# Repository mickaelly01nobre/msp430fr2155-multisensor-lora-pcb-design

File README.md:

# Nó Multissensor LoRa com MSP430 (PCB IoT de Baixo Consumo)

## 📌 Visão Geral
Este projeto apresenta o desenvolvimento de um **nó IoT multissensor de baixo consumo** baseado no **microcontrolador MSP430FR2155**, integrando múltiplos sensores ambientais e de monitoramento em uma PCB personalizada.

O sistema foi projetado com foco em **eficiência energética**, **comunicação sem fio** e **sensoriamento modular**, sendo adequado para aplicações como monitoramento ambiental, agricultura inteligente e sensoriamento remoto.

---

## ⚙️ Funcionalidades
- 🔋 **Projeto de Baixo Consumo**
  - Modos de sleep para sensores e MCU
  - Gerenciamento de energia otimizado para operação com bateria

- 📡 **Comunicação LoRa**
  - Transmissão de dados sem fio de longo alcance e baixo consumo

- 🌡️ **Integração Multissensor**
  - Sensor de temperatura e umidade
  - Sensor de gás
  - Sensor de peso (interface com célula de carga)

- 🔌 **Alimentação Flexível**
  - Entrada USB
  - Operação via bateria

- 🔄 **Confiabilidade do Sistema**
  - Circuito de reset externo para estabilidade do MCU
  - Interface de programação/debug

---

## 🧠 Arquitetura de Hardware
- **Microcontrolador:** MSP430FR2155  
- **Comunicação:** Módulo LoRa  
- **Sensores:**
  - Temperatura & Umidade  
  - Sensor de Gás  
  - Sensor de Peso (Célula de Carga)  

- **Sistema de Alimentação:**
  - Entrada USB  
  - Entrada por bateria  
  - Circuito de comutação de energia  

- **Outros Circuitos:**
  - Controle de alimentação dos sensores (sleep/power gating)  
  - Circuito de reset  
  - Interface de programação  

---

## 🔋 Estratégia de Baixo Consumo
O sistema foi projetado com foco em **eficiência energética**, incluindo:
- Ativação seletiva dos sensores (controle de modo sleep)
- Uso dos modos de baixo consumo do MSP430 (LPM)
- Seleção eficiente da fonte de energia (USB/Bateria)
- Redução do consumo em estado ocioso

---

## 🖥️ Projeto da PCB
- PCB personalizada desenvolvida para integração compacta  
- Separação das seções analógica e digital  
- Técnicas de redução de ruído para maior precisão dos sensores  
- Projetado utilizando (adicione seu software aqui: KiCad / Altium / etc.)  

---

## 📊 Aplicações
- Monitoramento ambiental  
- Agricultura inteligente  
- Sensoriamento industrial  
- Nós IoT remotos  

---

## 🚀 Melhorias Futuras
- Integração com plataformas em nuvem  
- Dashboard web/mobile  
- Suporte a energy harvesting  
- Otimização de firmware para ultra baixo consumo  

---

## 🛠️ Tecnologias & Habilidades
- Sistemas Embarcados  
- Projeto de PCB  
- Eletrônica de Baixo Consumo  
- Integração de Sensores  
- Sistemas IoT  
- Comunicação LoRa  

---

## 📷 Preview

---

## 👩‍💻 Autor
Desenvolvido por Mickaelly Freitas Nobre

---

# MSP430 LoRa Multisensor Node (Low Power IoT PCB)

## 📌 Overview
This project presents the design and development of a **low-power multisensor IoT node** based on the **MSP430FR2155 microcontroller**, integrating multiple environmental and monitoring sensors into a custom PCB.

The system is designed for **energy efficiency**, **wireless communication**, and **modular sensing**, making it suitable for applications such as environmental monitoring, smart agriculture, and remote sensing.

---

## ⚙️ Features
- 🔋 **Low Power Design**
  - Sleep modes for sensors and MCU
  - Power management optimized for battery operation

- 📡 **LoRa Communication**
  - Long-range, low-power wireless data transmission

- 🌡️ **Multisensor Integration**
  - Temperature and humidity sensor
  - Gas sensor
  - Weight sensor (load cell interface)

- 🔌 **Flexible Power Supply**
  - USB power input
  - Battery-powered operation

- 🔄 **System Reliability**
  - External reset circuit for MCU stability
  - Programming/debug interface

---

## 🧠 Hardware Architecture
- **Microcontroller:** MSP430FR2155  
- **Communication:** LoRa module  
- **Sensors:**
  - Temperature & Humidity  
  - Gas Sensor  
  - Weight Sensor (Load Cell)  

- **Power System:**
  - USB input  
  - Battery input  
  - Power switching circuit  

- **Other Circuits:**
  - Sensor power gating (sleep control)  
  - Reset circuit  
  - Programming interface  

---

## 🔋 Low Power Strategy
The system was designed with a focus on **energy efficiency**, including:
- Selective sensor activation (sleep mode control)
- MSP430 low-power modes (LPM)
- Efficient power path selection (USB/Battery)
- Reduced idle consumption

---

## 🖥️ PCB Design
- Custom PCB developed for compact integration  
- Separation of analog and digital sections  
- Noise reduction techniques for sensor accuracy  
- Designed using (add your software here: KiCad / Altium / etc.)

---

## 📊 Applications
- Environmental monitoring  
- Smart agriculture  
- Industrial sensing  
- Remote IoT nodes  

---

## 🚀 Future Improvements
- Integration with cloud platforms  
- Mobile/web dashboard  
- Energy harvesting support  
- Firmware optimization for ultra-low power  

---

---

## 🛠️ Technologies & Skills
- Embedded Systems  
- PCB Design  
- Low Power Electronics  
- Sensor Integration  
- IoT Systems  
- LoRa Communication  

---

## 📷 Preview

---

## 👩‍💻 Author
Developed by Mickaelly Freitas Nobre

---

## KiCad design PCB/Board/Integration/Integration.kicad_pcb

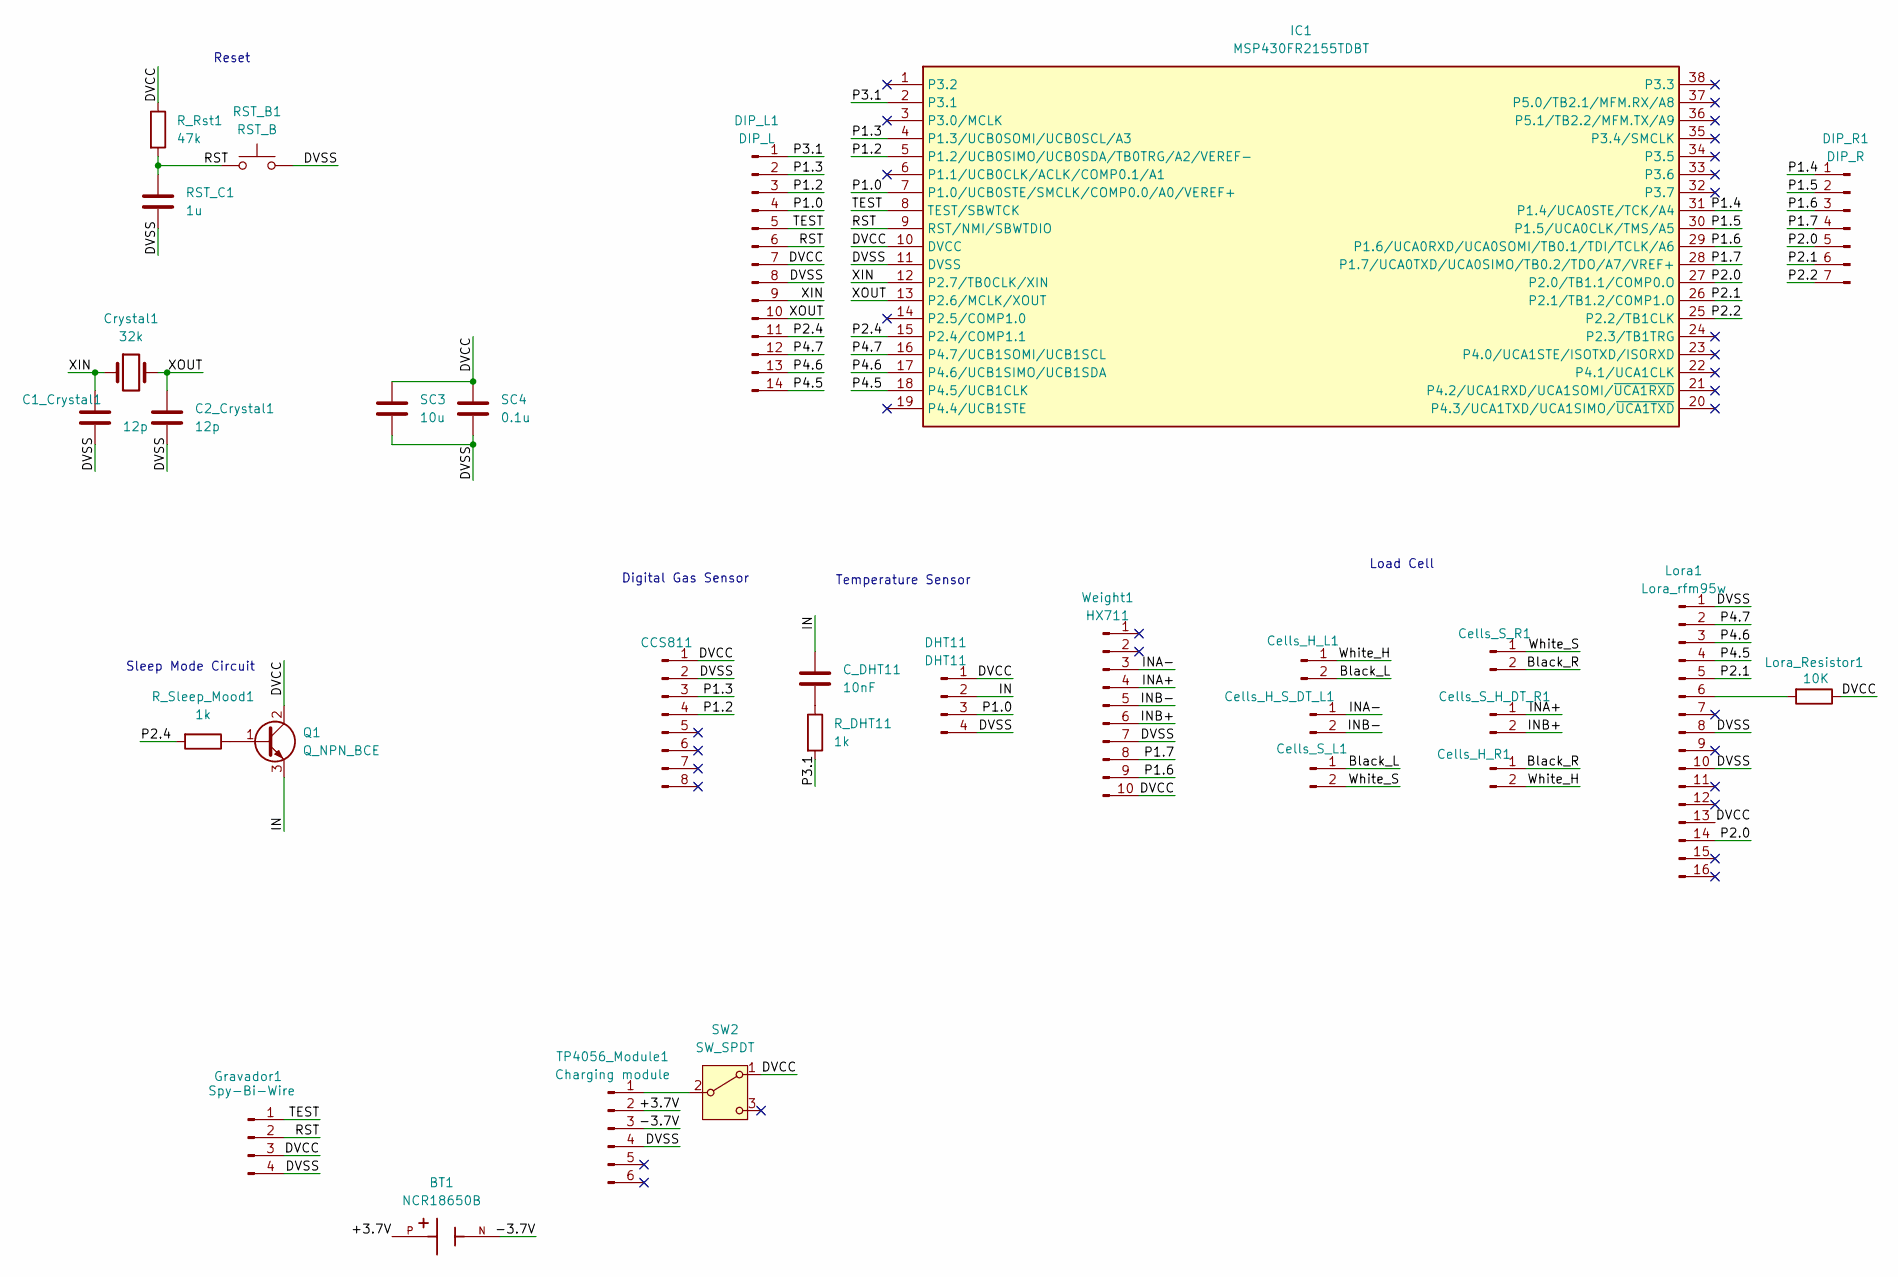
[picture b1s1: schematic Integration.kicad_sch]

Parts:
BT1: NCR18650B; BAT_1042; PARTREV E
C1_Crystal1, C2_Crystal1: 12p; C_Disc_D5.0mm_W2.5mm_P5.00mm
CCS811: Conn_01x08_Pin; MODULO_GAS
C_DHT11: 10nF; C_Disc_D3.0mm_W1.6mm_P2.50mm
Cells_H_L1: Conn_01x02_Pin; JST_XH_B2B-XH-A_1x02_P2.50mm_Vertical
Cells_H_R1: Conn_01x02_Pin; JST_XH_B2B-XH-A_1x02_P2.50mm_Vertical
Cells_H_S_DT_L1: Conn_01x02_Pin; JST_XH_B2B-XH-A_1x02_P2.50mm_Vertical
Cells_S_H_DT_R1: Conn_01x02_Pin; JST_XH_B2B-XH-A_1x02_P2.50mm_Vertical
Cells_S_L1: Conn_01x02_Pin; JST_XH_B2B-XH-A_1x02_P2.50mm_Vertical
Cells_S_R1: Conn_01x02_Pin; JST_XH_B2B-XH-A_1x02_P2.50mm_Vertical
Crystal1: 32k; R_Axial_DIN0204_L3.6mm_D1.6mm_P1.90mm_Vertical
DHT11: DHT11; Aosong_DHT11_5.5x12.0_P2.54mm
DIP_L1: DIP_L; PinSocket_1x14_P2.54mm_Vertical
DIP_R1: DIP_R; PinSocket_1x07_P2.54mm_Vertical
Gravador1: Spy-Bi-Wire; JST_XH_B4B-XH-A_1x04_P2.50mm_Vertical
IC1: MSP430FR2155TDBT; SOP50P640X120-38N; Mouser Part Number 595-MSP430FR2155TDBT
Lora1: Lora_rfm95w; HOPERF_RFM9XW_THT
Lora_Resistor1: 10K; R_Axial_DIN0204_L3.6mm_D1.6mm_P1.90mm_Vertical
Q1: Q_NPN_BCE; PinSocket_1x03_P2.54mm_Vertical
RST_B1: RST_B; SW_PUSH_6mm
RST_C1: 1u; CP_Radial_D8.0mm_P5.00mm
R_DHT11: 1k; R_Axial_DIN0204_L3.6mm_D1.6mm_P1.90mm_Vertical
R_Rst1: 47k; R_Axial_DIN0204_L3.6mm_D1.6mm_P1.90mm_Vertical
R_Sleep_Mood1: 1k; R_Axial_DIN0204_L3.6mm_D1.6mm_P1.90mm_Vertical
SC3: 10u; CP_Radial_D8.0mm_P3.50mm
SC4: 0.1u; C_Disc_D5.0mm_W2.5mm_P5.00mm
SW2: SW_SPDT; SW_PUSH_1P1T_6x3.5mm_H5.0_APEM_MJTP1250
TP4056_Module1: Charging module; TP4056
Weight1: HX711; MODULO_HX711

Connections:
/+3.7V: BT1.P, TP4056_Module1.2
/-3.7V: BT1.N, TP4056_Module1.3
/Black_L: Cells_H_L1.2, Cells_S_L1.1
/Black_R: Cells_H_R1.1, Cells_S_R1.2
/DVCC: CCS811.1, DHT11.1, DIP_L1.7, Gravador1.3, IC1.10 (DVCC), Lora1.13, Lora_Resistor1.1, Q1.2 (C), R_Rst1.1, SC3.1, SC4.1, SW2.1 (A), Weight1.10
/DVSS: C1_Crystal1.2, C2_Crystal1.2, CCS811.2, DHT11.4, DIP_L1.8, Gravador1.4, IC1.11 (DVSS), Lora1.1, Lora1.8, Lora1.10, RST_B1.2, RST_C1.2, SC3.2, SC4.2, TP4056_Module1.4, Weight1.7
/IN: C_DHT11.1, DHT11.2, Q1.3 (E)
/INA+: Cells_S_H_DT_R1.1, Weight1.4
/INA-: Cells_H_S_DT_L1.1, Weight1.3
/INB+: Cells_S_H_DT_R1.2, Weight1.6
/INB-: Cells_H_S_DT_L1.2, Weight1.5
/P1.0: DHT11.3, DIP_L1.4, IC1.7 (P1.0/UCB0STE/SMCLK/COMP0.0/A0/VEREF+)
/P1.2: CCS811.4, DIP_L1.3, IC1.5 (P1.2/UCB0SIMO/UCB0SDA/TB0TRG/A2/VEREF-)
/P1.3: CCS811.3, DIP_L1.2, IC1.4 (P1.3/UCB0SOMI/UCB0SCL/A3)
/P1.4: DIP_R1.1, IC1.31 (P1.4/UCA0STE/TCK/A4)
/P1.5: DIP_R1.2, IC1.30 (P1.5/UCA0CLK/TMS/A5)
/P1.6: DIP_R1.3, IC1.29 (P1.6/UCA0RXD/UCA0SOMI/TB0.1/TDI/TCLK/A6), Weight1.9
/P1.7: DIP_R1.4, IC1.28 (P1.7/UCA0TXD/UCA0SIMO/TB0.2/TDO/A7/VREF+), Weight1.8
/P2.0: DIP_R1.5, IC1.27 (P2.0/TB1.1/COMP0.O), Lora1.14
/P2.1: DIP_R1.6, IC1.26 (P2.1/TB1.2/COMP1.O), Lora1.5
/P2.2: DIP_R1.7, IC1.25 (P2.2/TB1CLK)
/P2.4: DIP_L1.11, IC1.15 (P2.4/COMP1.1), R_Sleep_Mood1.2
/P3.1: DIP_L1.1, IC1.2 (P3.1), R_DHT11.2
/P4.5: DIP_L1.14, IC1.18 (P4.5/UCB1CLK), Lora1.4
/P4.6: DIP_L1.13, IC1.17 (P4.6/UCB1SIMO/UCB1SDA), Lora1.3
/P4.7: DIP_L1.12, IC1.16 (P4.7/UCB1SOMI/UCB1SCL), Lora1.2
/RST: DIP_L1.6, Gravador1.2, IC1.9 (RST/NMI/SBWTDIO), RST_B1.1, RST_C1.1, R_Rst1.2
/TEST: DIP_L1.5, Gravador1.1, IC1.8 (TEST/SBWTCK)
/White_H: Cells_H_L1.1, Cells_H_R1.2
/White_S: Cells_S_L1.2, Cells_S_R1.1
/XIN: C1_Crystal1.1, Crystal1.1, DIP_L1.9, IC1.12 (P2.7/TB0CLK/XIN)
/XOUT: C2_Crystal1.1, Crystal1.2, DIP_L1.10, IC1.13 (P2.6/MCLK/XOUT)
unnamed: C_DHT11.2, R_DHT11.1
unnamed: Lora1.6, Lora_Resistor1.2
unnamed: Q1.1 (B), R_Sleep_Mood1.1
unnamed: SW2.2 (B), TP4056_Module1.1

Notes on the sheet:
Load Cell
Reset
Digital Gas Sensor
Temperature Sensor
Sleep Mode Circuit

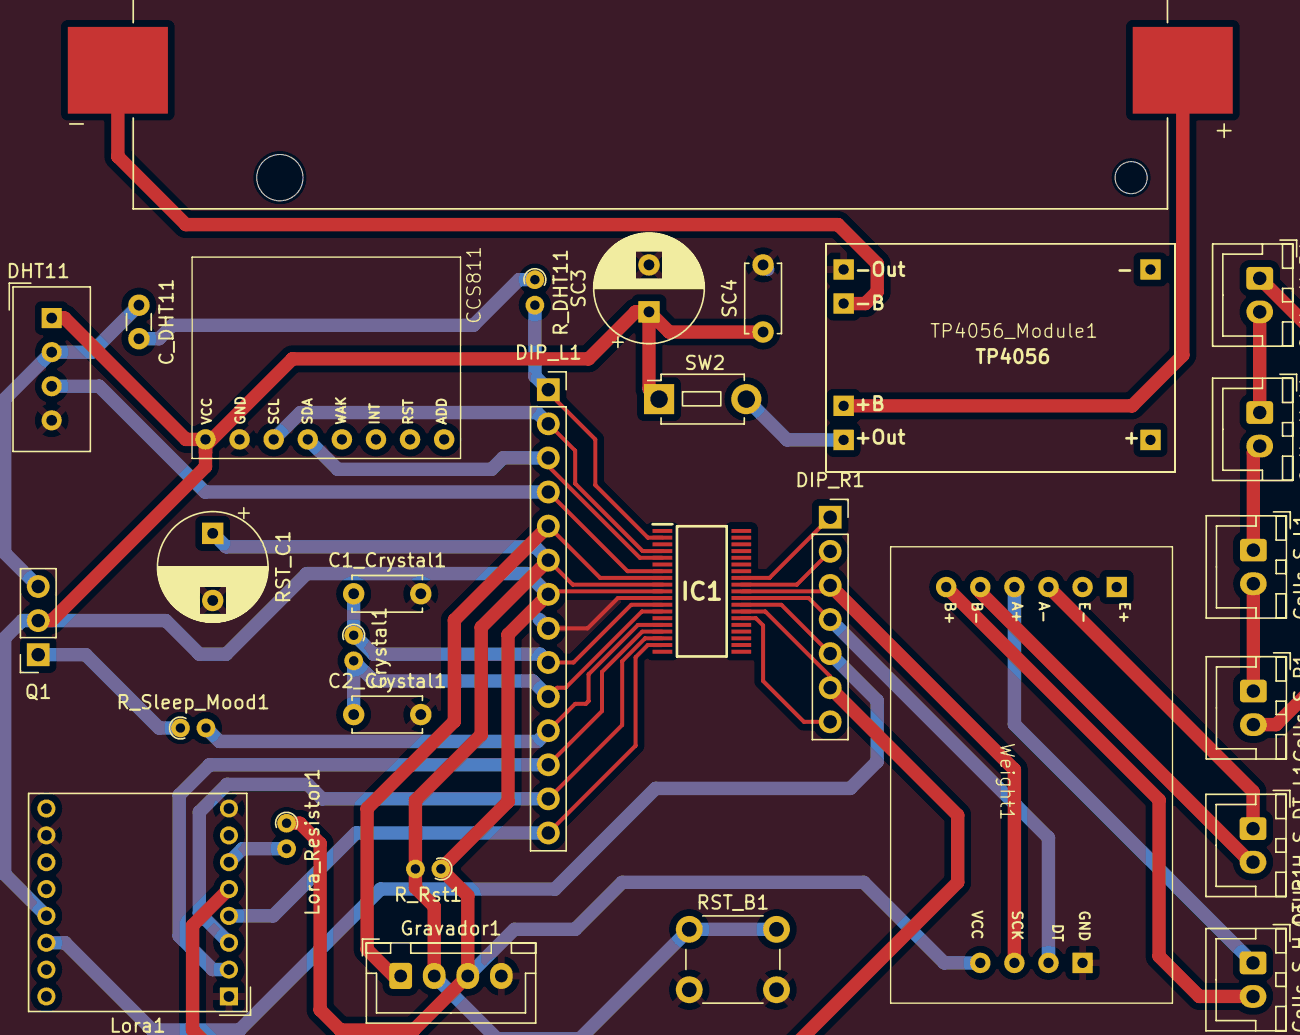
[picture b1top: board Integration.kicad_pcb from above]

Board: 2 copper layers, 30 parts (0 on the bottom side), 36 nets.

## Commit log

2026-04-14 Add more preview images to README
    Added additional preview images to the README.
2026-04-14 Remove duplicate board image from README
    Removed duplicate image entry from README.
